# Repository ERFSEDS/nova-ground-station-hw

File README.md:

# Ground_Station
This is the Repository for the Ground Station PCB, created November 2021

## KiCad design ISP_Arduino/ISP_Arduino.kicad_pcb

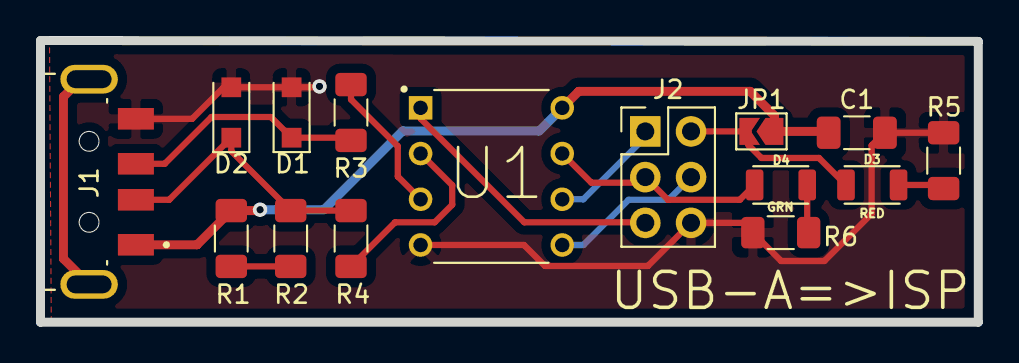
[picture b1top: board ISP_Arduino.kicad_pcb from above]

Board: 2 copper layers, 52.1 x 15.7 mm, 15 parts (0 on the bottom side), 15 nets.

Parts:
C1: 0.1mF; C_1206_3216Metric_Pad1.33x1.80mm_HandSolder
D1, D2: 3.3V; D_SOD-123F
D3: RED; RESC3015X65
D4: GRN; RESC3015X65
J1: 1-1734028-1; TE_1-1734028-1
J2: Conn_01x06_Male; PinHeader_2x03_P2.54mm_Vertical
JP1: SolderJumper_2_Open; SolderJumper-2_P1.3mm_Open_TrianglePad1.0x1.5mm
R1, R5: 1K; R_1206_3216Metric_Pad1.30x1.75mm_HandSolder
R2, R6: 499; R_1206_3216Metric_Pad1.30x1.75mm_HandSolder
R3, R4: 49; R_1206_3216Metric_Pad1.30x1.75mm_HandSolder
U1: ATTINY45-20PU; DIP787W46P254L927H533Q8

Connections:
/MISO: J2.1, U1.6
/MOSI: J2.4, U1.5
/RST: J2.5, U1.1
/SCK: D4.2, J2.3, U1.7
GND: C1.2, D1.2, D2.2, J1.4, J2.6, R5.2, R6.2, U1.4
unnamed: D1.1, J1.3, R3.2
unnamed: D2.1, J1.2, R2.2, R4.2
unnamed: D3.1, R5.1
unnamed: D3.2, J2.2, JP1.2
unnamed: D4.1, R6.1
unnamed: J1.S1, J1.S2
unnamed: R1.1, R2.1
unnamed: R3.1, U1.3
unnamed: R4.1, U1.2
VCC: C1.1, J1.1, JP1.1, R1.2, U1.8

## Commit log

2021-11-17 Made symbol & footprint
2021-11-17 More symbols & footprints yay
2021-11-17 Finished USB-A to ISP board
2022-01-26 Created GBR .zip file
